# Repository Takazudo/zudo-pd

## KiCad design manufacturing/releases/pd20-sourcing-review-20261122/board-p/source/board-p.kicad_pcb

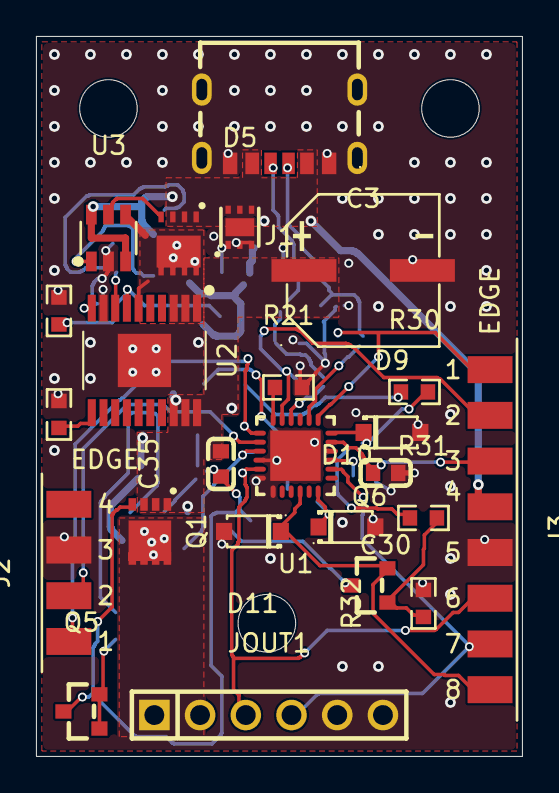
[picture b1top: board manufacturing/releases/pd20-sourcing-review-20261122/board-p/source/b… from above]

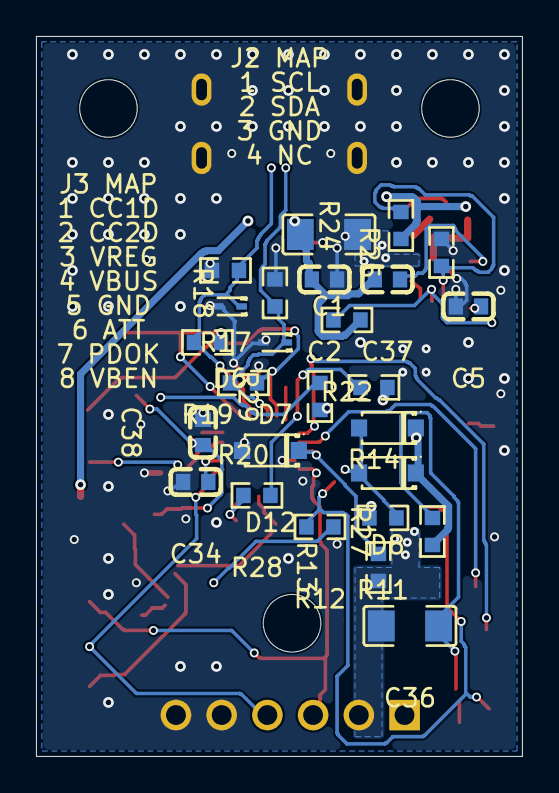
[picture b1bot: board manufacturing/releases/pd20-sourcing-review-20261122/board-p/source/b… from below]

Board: 2 copper layers, 27.0 x 40.0 mm, 53 parts (26 on the bottom side), 32 nets.

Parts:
C1: 10uF/50V; C1206
C2, C5, C35: 100nF/50V; C0603
C3: 100uF 50V; CAP-SMD_BD8.0-L8.3-W8.3-LS9.0-FD
C30, C34, C37, C38: 1uF/50V; C0603
C36: 1uF/50V X7R; C1206
D5: TVS2200DRVR; WSON-6_L2.0-W2.0-P0.65-BL-EP
D6, D7: PESD24VS1UB; SOD-523_L1.2-W0.8-LS1.6-RD
D8, D13: BZT52C11; SOD-123_Pad0.90x0.95mm_P3.15mm
D9, D11, D12: BZT52C18; SOD-123_Pad0.90x0.95mm_P3.15mm
D10: BZT52C20-7-F; SOD-123_L2.8-W1.8-LS3.7-RD
J1: TYPE-C-31-M-17; USB-C-SMD_10P-P1.00-L6.8-W8.9
J2: PogoPad_1x4_NVM_I2C; PogoPad_1x04_P2.54mm
J3: PogoPad_1x8_Debug; PogoPad_1x08_P2.54mm
JOUT1: 2.54mm 1x6 male; HDR-TH_6P-P2.54-V-M
MH1, MH2, MH3: MountingHole_3.2mm_M3
Q1: DMP3036SFG-7; PowerDI3333-8_DMP3036SFG
Q3: CSD18543Q3A; VSON-8_L3.3-W3.3-P0.65_CSD18543Q3A
Q5, Q6: BSS138-7-F; SOT-23_DIODES-DS30144-SUGGESTED
R11, R27: 150k; R0603
R12, R13: 4.7k; R0603
R14, R28, R29: 1k; R0603
R17, R18: 5.1k; R0603
R19, R20, R21: 0R; R0603
R22: 11.5k 0.1%; R0603
R23, R26: 4.02k 0.1%; R0603
R24: 174k 0.1%; R0603
R25: 10k 0.1%; R0603
R30: 470R; R0603
R31, R32: 100k; R0603
U1: STUSB4500QTR; QFN-24_L4.0-W4.0-P0.50-BL-EP2.8
U2: TPS16630PWPR; HTSSOP-20_PWP0020T_P0.65_EP2.96_TI-DRAFT
U3: LM74700QDBVRQ1; SOT-23-6_TI-DBV0006A

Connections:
ATT: J3.6, JOUT1.3, U1.11
CC1: D6.1, J1.3, R17.1, R19.2, U1.2
CC1DB: J3.1, R19.1, U1.1
CC2: D7.1, J1.4, R18.1, R20.2, U1.4
CC2DB: J3.2, R20.1, U1.5
DISCH: D12.1, R13.2, U1.9
EF_DVDT: C5.1, U2.10
EF_GATE: Q3.4, U3.5
EF_ILIM: R26.1, U2.11
EF_IN: Q3.5, Q3.6, Q3.7, Q3.8, Q3.9, U2.1, U2.2, U2.3, U2.6, U3.4
EF_OVP: R24.2, R25.1, U2.8
EF_UVLO: R22.2, R23.1, U2.7
EF_VCAP: C37.1, U3.1
GND: C1.1, C2.1, C3.2, C5.2, C30.1, C34.2, C38.2, D5.1, D5.2, D5.3, D5.7, D6.2, D7.2, D9.2, D10.2, D11.2, D12.2, J1.0, J1.1, J1.6, J2.3, J3.5, JOUT1.5, JOUT1.6, R17.2, R18.2, R21.2, R23.2, R25.2, R26.2, R32.2, U1.10, U1.12, U1.13, U1.22, U1.25, U2.9, U2.21, U3.2
PDOK: J3.7, JOUT1.4, U1.20
Q1_G: C35.1, D8.2, D13.2, Q1.4, Q5.3, R11.1, R12.2
Q1_MX: C36.1, Q5.1, Q5.2, R27.2
RESET: R21.1, U1.6
SCL: J2.1, U1.7
SDA: J2.2, U1.8
VBEN: Q6.3, R12.1
VBEN_PIN: D11.1, J3.8, Q6.2, U1.16
VBUS_DISCH_R: R14.2, R28.1
VBUS_IN: C1.2, C2.2, C37.2, D5.4, D5.5, D5.6, J1.2, J1.5, J3.4, Q3.1, Q3.2, Q3.3, R22.1, R24.1, U3.3, U3.6
VBUS_OUT: C36.2, JOUT1.1, JOUT1.2, Q1.5, Q1.6, Q1.7, Q1.8, Q1.9, R13.1
VBUS_P: C3.1, C35.2, D8.1, D13.1, Q1.1, Q1.2, Q1.3, R11.2, R14.1, R27.1, R29.1, U2.18, U2.19, U2.20
VBUS_VS_DISCH: D10.1, R28.2, U1.18
VDD_LOC: C38.1, D9.1, R30.2, R31.1, U1.24
VDD_MID: R29.2, R30.1
VG_LOC: Q6.1, R31.2, R32.1
VREG_1V2: C34.1, U1.21
VREG_2V7: C30.2, J3.3, U1.23

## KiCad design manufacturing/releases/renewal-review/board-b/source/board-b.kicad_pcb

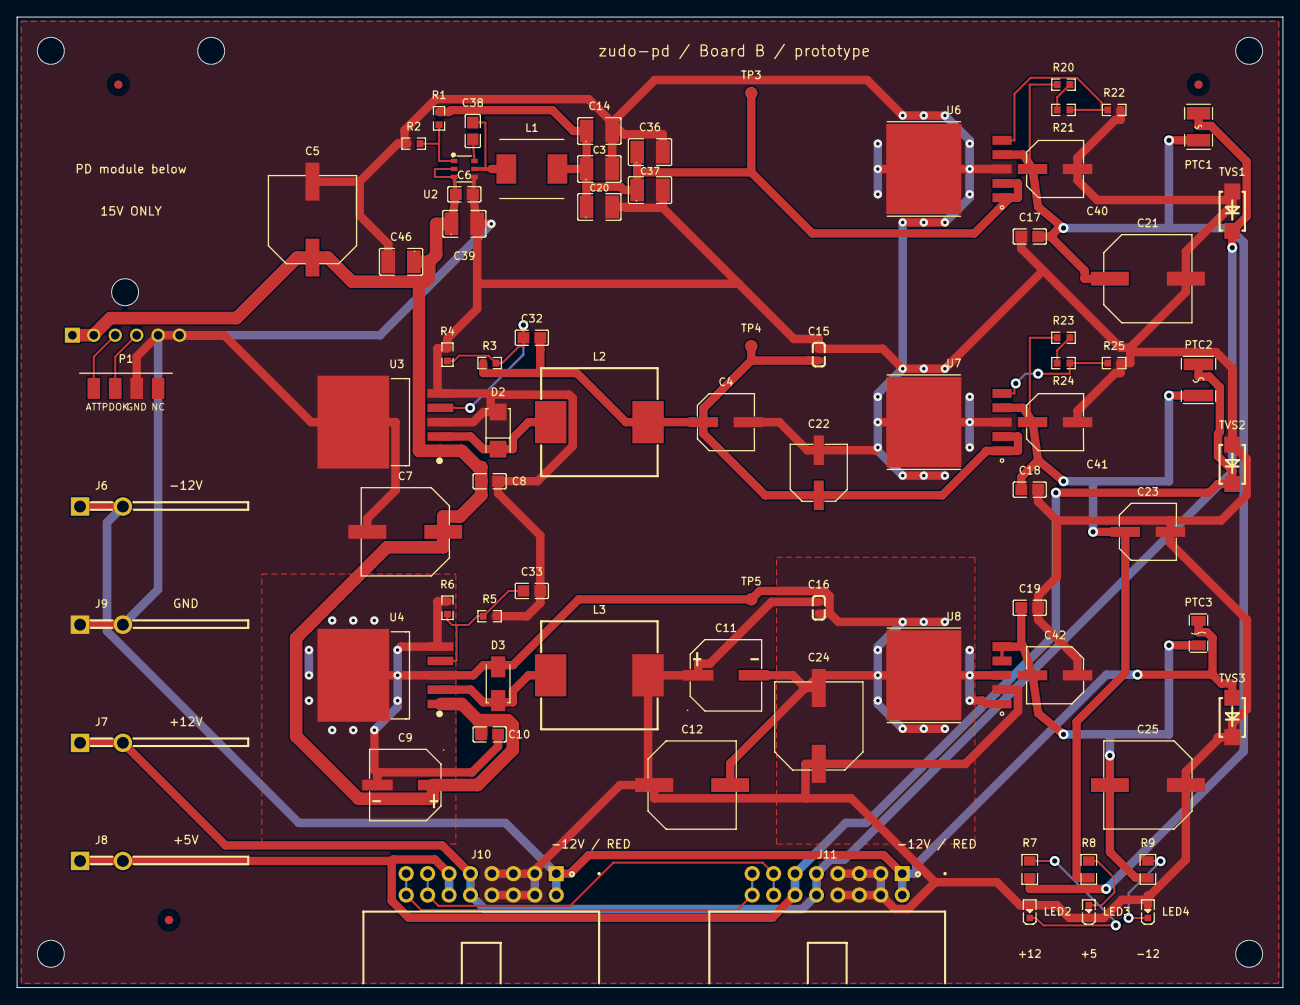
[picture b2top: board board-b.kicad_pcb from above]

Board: 2 copper layers, 150.0 x 115.0 mm, 87 parts (1 on the bottom side), 29 nets.

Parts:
C3, C14, C20, C36, C37, C39, C46: 10uF 50V X7R; C1210
C4, C22, C23: 470uF 10V; CAP-SMD_BD6.3-L6.6-W6.6-FD
C5, C7, C12, C21, C24, C25: 470uF 35V; CAP-SMD_BD10.0-L10.3-W10.3-LS11.0-FD
C6, C8, C10, C17, C18, C19, C38: 100nF 50V; C0805
C9: 100uF 50V; CAP-SMD_BD8.0-L8.3-W8.3-LS9.0-FD
C11: 470uF 25V; CAP-SMD_BD8.0-L8.3-W8.3-LS9.0-FD
C15, C16: 470nF; C0603
C32, C33: 22nF; C0805
C40, C41, C42: 47uF 25V polymer; CAP-SMD_BD6.3-L6.6-W6.6-FD
D2: SS34; SMA_L4.3-W2.6-LS5.2-RD
D3: SDT5A60SA-13; SMA_Diodes_SDT5A60SA_C3024223
FID1, FID2, FID3: Fiducial; Fiducial_1mm_Mask2mm
H1, H2, H3, H4, H5, H6: MountingHole_M3
J5: PM254V-11-06-H85; HDR-TH_6P-P2.54-V-F
J6, J7, J8, J9: 63951-1; CONN-TH_1217754-1
J10, J11: DW254P-2X8-L0; IDC-TH_16P-P2.54_321016RG0ABK00A01
L1: 10uH; ASPI-0630LR_L7.5-W6.85
L2, L3: 100uH; IND-SMD_L13.8-W12.8
LED2: Green; LED0603-RD
LED3: Blue; LED0603-RD
LED4: Red; LED0603-RD
P1: ATT/PDOK pads; PogoPad_1x04_P2.54mm
PTC1: SMD1210P150TF/16; F1210
PTC2: mSMD110-33V; F1812
PTC3: BSMD1206-150-16V; F1206
R1: 158k 0.1%; R0603
R2: 10k 0.1%; R0603
R3: 4300R; R0603
R4: 1k; R0603
R5: 10500R; R0603
R6: 1000R; R0603
R7, R8, R9: 1k; R0805
R20: 8200R 0.1%; R0603
R21: 680R 0.1%; R0603
R22, R25: 1000R 0.1%; R0603
R23: 3090R 0.1%; R0603
R24: 33R 0.1%; R0603
TP3: +13.44V; TestPad_D1.5mm
TP4: +6.519V; TestPad_D1.5mm
TP5: -14.145V; TestPad_D1.5mm
TVS1, TVS3: SMAJ15A; D-FLAT_L4.3-W2.6-LS5.3-RD
TVS2: SMAJ6.5A; D-FLAT_L4.3-W2.6-LS5.3-RD
U2: AP63201WU-7; TSOT-23-6_L2.9-W1.6-P0.95-LS2.8-BR
U3, U4: LM2596S-ADJ; TO-263-5_L10.2-W8.9-P1.70-BR
U6, U7: LT1963AEQ#PBF; TO-263-5_L10.6-W9.6-P1.70-LS15.9-BR
U8: LT3015EQ-12#PBF; DD-PAK-5_L10.2-W8.9-P1.70-LS14.0-BR

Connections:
+5V rail: J8.1, J8.2, J10.11, J10.12, J11.11, J11.12, PTC2.2, TVS2.1
+12V rail: J7.1, J7.2, J10.9, J10.10, J11.9, J11.10, PTC1.2, TVS1.1
+15V INPUT: C5.1, C6.1, C7.1, C8.1, C9.1, C10.1, C39.1, C46.1, J5.1, J5.2, U2.2, U2.3, U3.1, U4.1
-12V rail: J6.1, J6.2, J10.1, J10.2, J11.1, J11.2, PTC3.2, TVS3.2
ATT: J5.3, P1.1
CV rail: J10.13, J10.14, J11.13, J11.14
GATE rail: J10.15, J10.16, J11.15, J11.16
GND: C3.2, C4.2, C5.2, C6.2, C7.2, C8.2, C11.1, C12.1, C14.2, C15.2, C16.2, C17.1, C18.2, C19.2, C20.2, C21.2, C22.2, C23.2, C24.1, C25.1, C33.2, C36.2, C37.2, C39.2, C40.2, C41.2, C42.1, C46.2, D2.2, J5.5, J5.6, J9.1, J9.2, J10.3, J10.4, J10.5, J10.6, J10.7, J10.8, J11.3, J11.4, J11.5, J11.6, J11.7, J11.8, L3.2, LED2.2, LED3.1, LED4.2, P1.3, R2.1, R4.2, R5.2, R22.2, R25.2, TVS1.2, TVS2.2, TVS3.1, U2.4, U3.3, U3.5, U3.6, U6.3, U6.6, U7.3, U7.6, U8.2
unnamed: D2.1, L2.1, U3.2
unnamed: D3.1, L3.1, U4.2
unnamed: LED2.1, R7.2
unnamed: LED3.2, R8.2
unnamed: LED4.1, R9.2
unnamed: R1.1, R2.2, U2.1
unnamed: C32.1, R3.2, R4.1, U3.4
unnamed: C33.1, R5.1, R6.1, U4.4
unnamed: C17.2, C21.1, C40.1, PTC1.1, R7.1, R20.1, U6.4
unnamed: C18.1, C23.1, C41.1, PTC2.1, R8.1, R23.1, U7.4
unnamed: C19.1, C25.2, C42.2, PTC3.1, R9.1, U8.4, U8.5
PDOK: J5.4, P1.2
U2_BST: C38.1, U2.6
U2_SW: C38.2, L1.1, U2.5
U6 ADJ: R21.2, R22.1, U6.5
U6 FB upper series: R20.2, R21.1
U7 ADJ: R24.2, R25.1, U7.5
U7 FB upper series: R23.2, R24.1
/DC-DC Conversion/+6.519V PRE: C4.1, C15.1, C22.1, C32.2, L2.2, R3.1, TP4.1, U7.1, U7.2
/DC-DC Conversion/+13.44V PRE: C3.1, C14.1, C20.1, C36.1, C37.1, L1.2, R1.2, TP3.1, U6.1, U6.2
/DC-DC Conversion/-14.145V PRE: C9.2, C10.2, C11.2, C12.2, C16.1, C24.2, D3.2, R6.2, TP5.1, U4.3, U4.5, U4.6, U8.1, U8.3, U8.6

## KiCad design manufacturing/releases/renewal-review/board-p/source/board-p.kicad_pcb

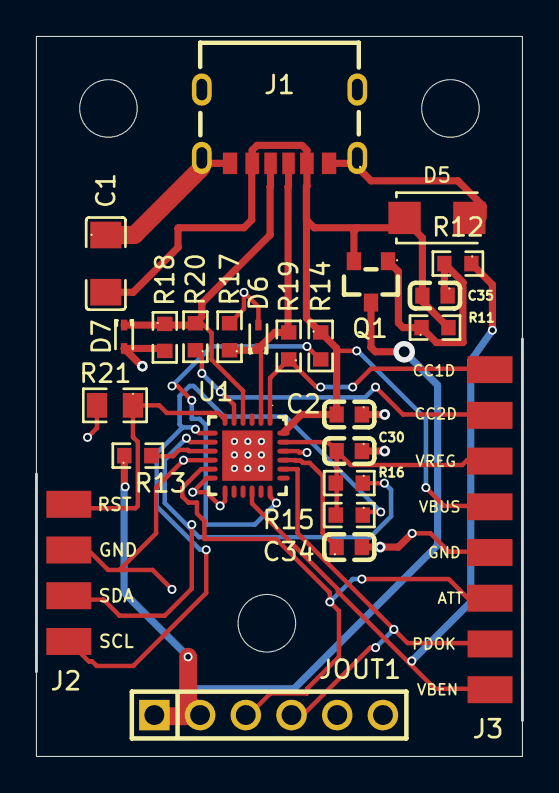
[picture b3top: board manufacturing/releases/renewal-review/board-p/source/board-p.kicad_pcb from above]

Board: 2 copper layers, 27.0 x 40.0 mm, 28 parts (0 on the bottom side), 18 nets.

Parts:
C1: 10uF/50V; C1206
C2, C35: 100nF/50V; C0603
C30, C34: 1uF/50V; C0603
D5: SMAJ16A-E3/61; SMA_Vishay_SMAJ16A_C968650
D6, D7: PESD24VS1UB; SOD-523_L1.2-W0.8-LS1.6-RD
J1: TYPE-C-31-M-17; USB-C-SMD_10P-P1.00-L6.8-W8.9
J2: PogoPad_1x4_NVM_I2C; PogoPad_1x04_P2.54mm
J3: PogoPad_1x8_Debug; PogoPad_1x08_P2.54mm
JOUT1: 2.54mm 1x6 male; HDR-TH_6P-P2.54-V-M
MH1, MH2, MH3: MountingHole_3.2mm_M3
Q1: AO3401A; SOT-23_L2.9-W1.3-P1.90-LS2.4-BR
R11: 100k; R0603
R12: 150k; R0603
R13, R14: 470R; R0603
R15, R16: 4.7k; R0603
R17, R18: 5.1k; R0603
R19, R20: 0R; R0603
R21: 10k; R0805
U1: STUSB4500QTR; QFN-24_L4.0-W4.0-P0.50-BL-EP2.8

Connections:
ATT: J3.6, JOUT1.3, U1.11 (ATTACH)
CC1: D6.1 (C), J1.3 (A5), R17.1, R19.2, U1.2 (CC1)
CC1DB: J3.1, R19.1, U1.1 (CC1DB)
CC2: D7.1 (C), J1.4 (B5), R18.1, R20.2, U1.4 (CC2)
CC2DB: J3.2, R20.1, U1.5 (CC2DB)
DISCH: R13.2, U1.9 (DISCH)
GND: C1.1, C2.1, C30.1, C34.2, D5.2, D6.2 (A), D7.2 (A), J1.0, J1.1 (B12), J1.6 (A12), J2.3, J3.5, JOUT1.5, JOUT1.6, R17.2, R18.2, R21.2, U1.10 (GND), U1.12 (ADDR0), U1.13 (ADDR1), U1.22 (VSYS), U1.25 (EP)
PDOK: J3.7, JOUT1.4, U1.20 (POWER_OK2)
Q1_G: C35.1, Q1.1 (G), R11.1, R12.2
RESET: J2.4, R21.1, U1.6 (RESET)
SCL: J2.1, R15.1, U1.7 (SCL)
SDA: J2.2, R16.1, U1.8 (SDA)
VBEN: J3.8, R12.1, U1.16 (VBUS_EN_SNK)
VBUS_IN: C1.2, C2.2, C35.2, D5.1, J1.2 (B9), J1.5 (A9), J3.4, Q1.2 (S), R11.2, R14.1, U1.24 (VDD)
VBUS_OUT: JOUT1.1, JOUT1.2, Q1.3 (D), R13.1
VBUS_VS_DISCH: R14.2, U1.18 (VBUS_VS_DISCH)
VREG_1V2: C34.1, U1.21 (VREG_1V2)
VREG_2V7: C30.2, J3.3, R15.2, R16.2, U1.23 (VREG_2V7)
